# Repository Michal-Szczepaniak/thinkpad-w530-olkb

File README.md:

# Thinkpad OLKB Preonic keybaord pcb

Get it printed and enjoy.

USB can be connected in multiple ways:

- Directly into the MCU thanks to open space near it
- After soldering the bottom pads, via available pins next to the usb port
- After soldering the bottom pads and FPC connector, via FPC connector

USB can be fetched from multiple places, the lower end the laptop (x series) the less options so I'll list all the w530 options:

- Bluetooth connector, if you swapped wifi card for wifi+bt you aren't using the standalone bt so you can get usb from there
- msata, its next to the open hole for the usb, with msata to usb converter you can either just plug in short cable from msata directly to mcu (easiest possible connection) or you can cut the microusb end and solder it to pins or desolder the usb and route it with wires
- Smartcard fpc connector, it's located at the bottom middle of the motheboard next to the bios chips underneath the touchpad. Thats what the FPC connector on keyboard is for, you can buy 6 pin 0.5mm pitch FPC cable and connect it. Watch out though because it has 5V 15A unfused and if you short it you will instantly kill the laptop, but the keyboard has fuse which protects it, but only if something happens AFTER the fuse so isolate the fpc connector pins.
- Fingerprint/color sensor usb FPC, they're both just usb's on FPC tape, so you can use that, although they might not be directly pluggable into keyboard's FPC connector, I don't know their pinout as I was targetting the Smartcard FPC connector.

Power button is connected via mounting OG keyboard's FPC tape or soldering it, you can pick either option by soldering the pads next to the FPC pins. Make sure you pick correct option otherwise you can short something. Power button is also routed to the mcu pin in case you want that, although when laptop is off, they keyboard is off unless you route always-on 5V to it.

There are pins for connecting Framework touchpad, if you go this route, just wire them to the test pads on the Framework's touchpad and that's it. If you want to use Framework's touchpad and mount it by demeling the case then you need to break out the touchpad pcb extension.

There's hole for a keyboard mounting screw, M2x20 and use a nut to hold it down but don't overtighten it!

Oh also cake the bottom in electrical tape and make sure there are no pointy solder points, otherwise it will short out on the aluminum case which is less than ideal.

As of now the space above keyboard is not covered by anything which is KIIIIIIINDA sketchy but can be covered with electrical tape or simple 3D print. If you don't use the hole for usb cable that one can also be covered via electrical tape.

# 3D Printable blanks

Because the keyboard has gaping hole in the middle for the usb cable and also gaping hole above it, there are 3D printable blanks that can be put in place to protect anything below. Also if you decide to mod the touchpad I've included the touchpad buttons blank. [Blanks directory](https://github.com/Michal-Szczepaniak/thinkpad-w530-olkb)

# BOM 

- FPC 6PIN 0.5mm pitch, opposite side. Also please be careful because if you wire it incorrectly you'll instantly fry the motherboard.
- 6 pin FPC connector - DS1020-11-6VBT1-R
- Raspberry pi pico
- PG1425 switches
- Either THT or SMD diodes - THT you can handle, SMD 1N4148WS-DIO (SOD323F)
- Patience

# Palm rejection not working 

By default both framework touchpad and this keyboard are treated as external devices so we have to tell libinput that they're in fact not.

Create file `/etc/libinput/local-overrides.quirks` with content:
```
[Keyboards]
MatchUdevType=keyboard
MatchName=QMK Macroboard
AttrKeyboardIntegration=internal

[Touchpad]
MatchUdevType=touchpad
MatchName=QMK Macroboard Touchpad
AttrKeyboardIntegration=internal
```

And enable palm rejection. Voila!

# Gallery

## Schematic

## Board

## 3D View

## Real photo

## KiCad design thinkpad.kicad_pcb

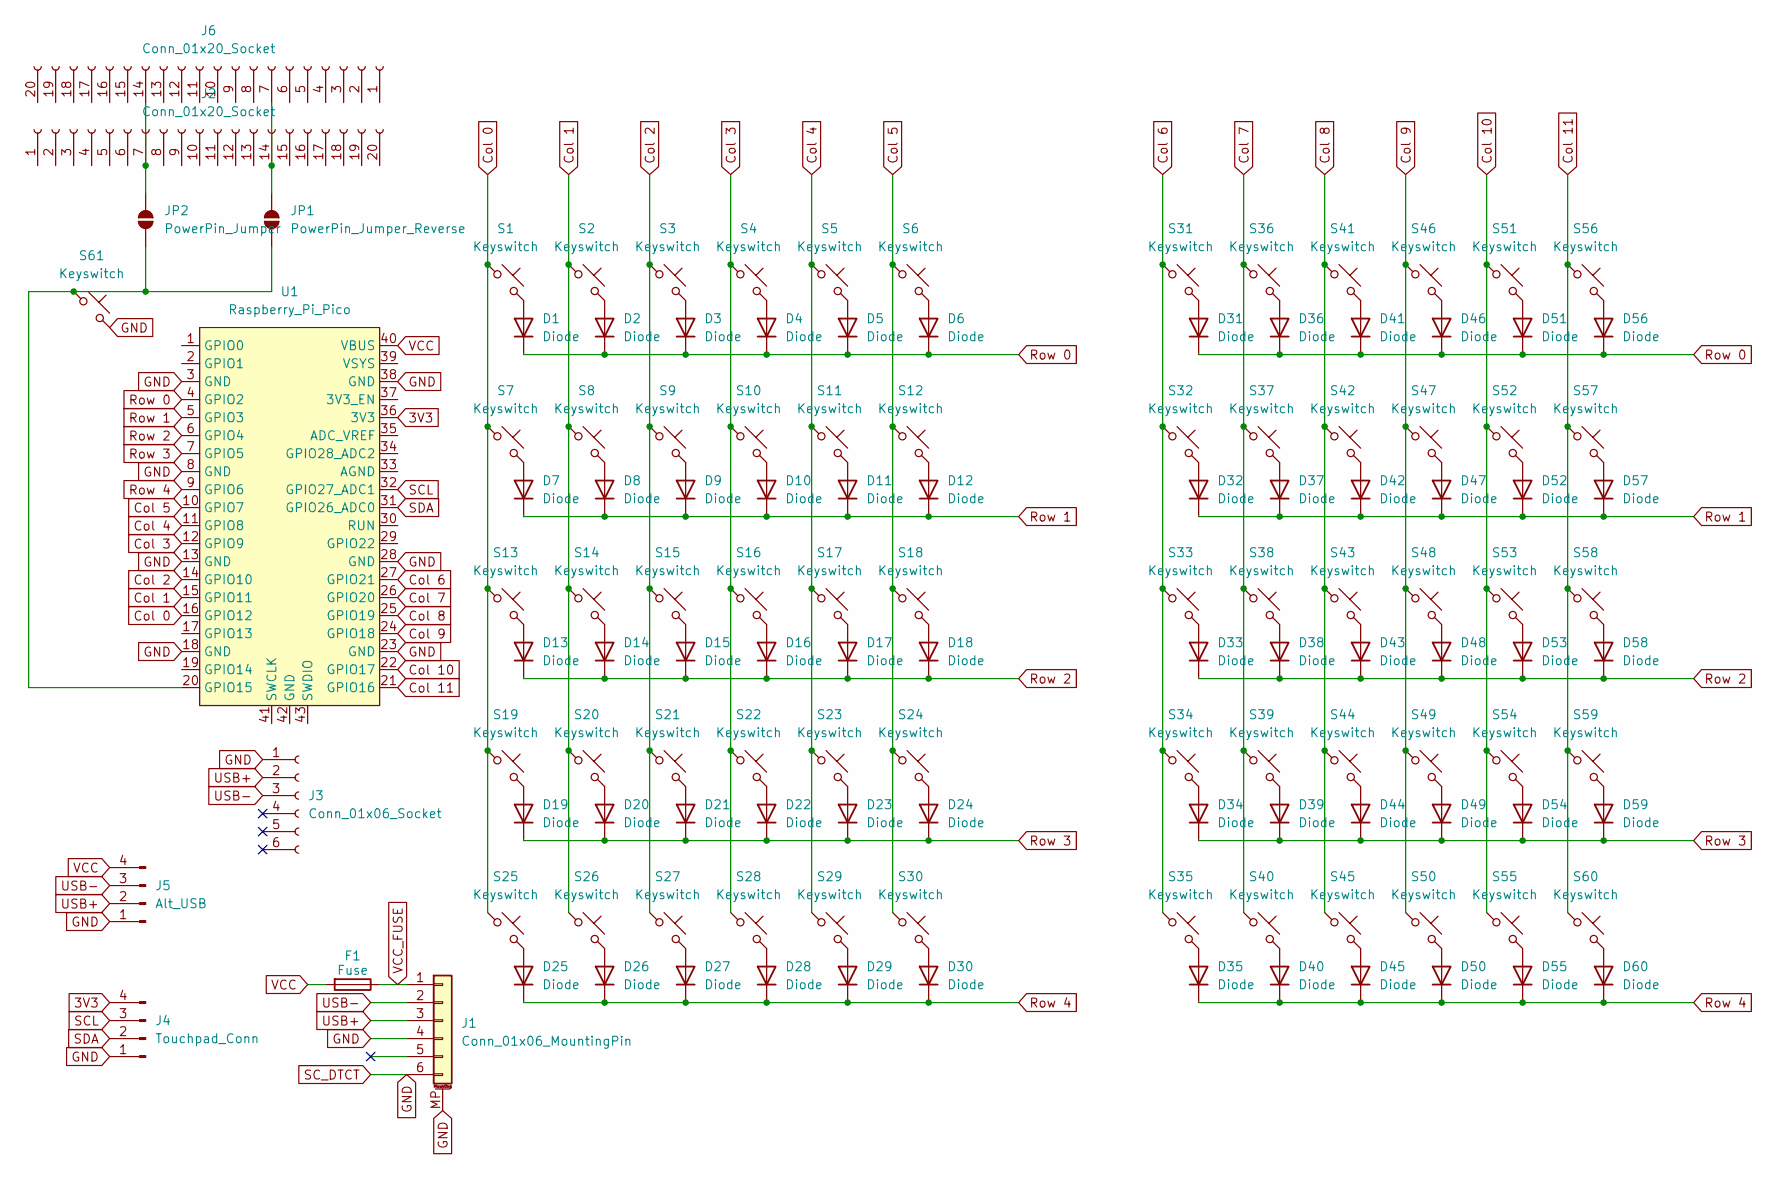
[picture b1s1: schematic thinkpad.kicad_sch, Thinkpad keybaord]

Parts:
D1, D2, D3, D4, D5, D6, D7, D8, D9, D10, D11, D12, D13, D14, D15, D16, D17, D18, D19, D20, D21, D22, D23, D24, D25, D26, D27, D28, D29, D30, D31, D32, D33, D34, D35, D36, D37, D38, D39, D40, D41, D42, D43, D44, D45, D46, D47, D48, D49, D50, D51, D52, D53, D54, D55, D56, D57, D58, D59, D60: Diode; Diode_SMD_THT2
F1: Fuse; Fuse_0805_2012Metric
J1: Conn_01x06_MountingPin; FPC_6
J2, J6: Conn_01x20_Socket; Thinkpad-keyboard-fpc
J3: Conn_01x06_Socket; pi pico usb
J4: Touchpad_Conn; PinHeader_1x04_P2.54mm_Vertical
J5: Alt_USB; PinHeader_1x04_P2.54mm_Vertical
JP1: PowerPin_Jumper_Reverse; SolderJumper-2_P1.3mm_Open_Pad1.0x1.5mm
JP2: PowerPin_Jumper; SolderJumper-2_P1.3mm_Open_Pad1.0x1.5mm
S1, S2, S3, S4, S5, S6, S7, S8, S9, S10, S11, S12, S13, S14, S15, S16, S17, S18, S19, S20, S21, S22, S23, S24, S25, S26, S27, S28, S29, S30, S31, S32, S33, S34, S35, S36, S37, S38, S39, S40, S41, S42, S43, S44, S45, S46, S47, S48, S49, S50, S51, S52, S53, S54, S55, S56, S57, S58, S59, S60, S61: Keyswitch; Kailh-PG1425-X-Switch
U1: Raspberry_Pi_Pico

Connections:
3V3: J4.4, U1.36 (3V3)
Col 0: S1.1, S7.1, S13.1, S19.1, S25.1, U1.16 (GPIO12)
Col 1: S2.1, S8.1, S14.1, S20.1, S26.1, U1.15 (GPIO11)
Col 2: S3.1, S9.1, S15.1, S21.1, S27.1, U1.14 (GPIO10)
Col 3: S4.1, S10.1, S16.1, S22.1, S28.1, U1.12 (GPIO9)
Col 4: S5.1, S11.1, S17.1, S23.1, S29.1, U1.11 (GPIO8)
Col 5: S6.1, S12.1, S18.1, S24.1, S30.1, U1.10 (GPIO7)
Col 6: S31.1, S32.1, S33.1, S34.1, S35.1, U1.27 (GPIO21)
Col 7: S36.1, S37.1, S38.1, S39.1, S40.1, U1.26 (GPIO20)
Col 8: S41.1, S42.1, S43.1, S44.1, S45.1, U1.25 (GPIO19)
Col 9: S46.1, S47.1, S48.1, S49.1, S50.1, U1.24 (GPIO18)
Col 10: S51.1, S52.1, S53.1, S54.1, S55.1, U1.22 (GPIO17)
Col 11: S56.1, S57.1, S58.1, S59.1, S60.1, U1.21 (GPIO16)
GND: J1.4, J1.6, J1.MP (MountPin), J3.1, J4.1, J5.1, S61.2, U1.3 (GND), U1.8 (GND), U1.13 (GND), U1.18 (GND), U1.23 (GND), U1.28 (GND), U1.38 (GND)
unnamed: D1.2 (A), S1.2
unnamed: D2.2 (A), S2.2
unnamed: D3.2 (A), S3.2
unnamed: D4.2 (A), S4.2
unnamed: D5.2 (A), S5.2
unnamed: D6.2 (A), S6.2
unnamed: D7.2 (A), S7.2
unnamed: D8.2 (A), S8.2
unnamed: D9.2 (A), S9.2
unnamed: D10.2 (A), S10.2
unnamed: D11.2 (A), S11.2
unnamed: D12.2 (A), S12.2
unnamed: D13.2 (A), S13.2
unnamed: D14.2 (A), S14.2
unnamed: D15.2 (A), S15.2
unnamed: D16.2 (A), S16.2
unnamed: D17.2 (A), S17.2
unnamed: D18.2 (A), S18.2
unnamed: D19.2 (A), S19.2
unnamed: D20.2 (A), S20.2
unnamed: D21.2 (A), S21.2
unnamed: D22.2 (A), S22.2
unnamed: D23.2 (A), S23.2
unnamed: D24.2 (A), S24.2
unnamed: D25.2 (A), S25.2
unnamed: D26.2 (A), S26.2
unnamed: D27.2 (A), S27.2
unnamed: D28.2 (A), S28.2
unnamed: D29.2 (A), S29.2
unnamed: D30.2 (A), S30.2
unnamed: D31.2 (A), S31.2
unnamed: D32.2 (A), S32.2
unnamed: D33.2 (A), S33.2
unnamed: D34.2 (A), S34.2
unnamed: D35.2 (A), S35.2
unnamed: D36.2 (A), S36.2
unnamed: D37.2 (A), S37.2
unnamed: D38.2 (A), S38.2
unnamed: D39.2 (A), S39.2
unnamed: D40.2 (A), S40.2
unnamed: D41.2 (A), S41.2
unnamed: D42.2 (A), S42.2
unnamed: D43.2 (A), S43.2
unnamed: D44.2 (A), S44.2
unnamed: D45.2 (A), S45.2
unnamed: D46.2 (A), S46.2
unnamed: D47.2 (A), S47.2
unnamed: D48.2 (A), S48.2
unnamed: D49.2 (A), S49.2
unnamed: D50.2 (A), S50.2
unnamed: D51.2 (A), S51.2
unnamed: D52.2 (A), S52.2
unnamed: D53.2 (A), S53.2
unnamed: D54.2 (A), S54.2
unnamed: D55.2 (A), S55.2
unnamed: D56.2 (A), S56.2
unnamed: D57.2 (A), S57.2
unnamed: D58.2 (A), S58.2
unnamed: D59.2 (A), S59.2
unnamed: D60.2 (A), S60.2
unnamed: J2.7, J6.14, JP2.2 (B)
unnamed: J2.14, J6.7, JP1.2 (B)
unnamed: JP1.1 (A), JP2.1 (A), S61.1, U1.20 (GPIO15)
Row 0: D1.1 (K), D2.1 (K), D3.1 (K), D4.1 (K), D5.1 (K), D6.1 (K), D31.1 (K), D36.1 (K), D41.1 (K), D46.1 (K), D51.1 (K), D56.1 (K), U1.4 (GPIO2)
Row 1: D7.1 (K), D8.1 (K), D9.1 (K), D10.1 (K), D11.1 (K), D12.1 (K), D32.1 (K), D37.1 (K), D42.1 (K), D47.1 (K), D52.1 (K), D57.1 (K), U1.5 (GPIO3)
Row 2: D13.1 (K), D14.1 (K), D15.1 (K), D16.1 (K), D17.1 (K), D18.1 (K), D33.1 (K), D38.1 (K), D43.1 (K), D48.1 (K), D53.1 (K), D58.1 (K), U1.6 (GPIO4)
Row 3: D19.1 (K), D20.1 (K), D21.1 (K), D22.1 (K), D23.1 (K), D24.1 (K), D34.1 (K), D39.1 (K), D44.1 (K), D49.1 (K), D54.1 (K), D59.1 (K), U1.7 (GPIO5)
Row 4: D25.1 (K), D26.1 (K), D27.1 (K), D28.1 (K), D29.1 (K), D30.1 (K), D35.1 (K), D40.1 (K), D45.1 (K), D50.1 (K), D55.1 (K), D60.1 (K), U1.9 (GPIO6)
SCL: J4.3, U1.32 (GPIO27_ADC1)
SDA: J4.2, U1.31 (GPIO26_ADC0)
USB+: J1.3, J3.2, J5.2
USB-: J1.2, J3.3, J5.3
VCC: F1.2, J5.4, U1.40 (VBUS)
VCC_FUSE: F1.1, J1.1

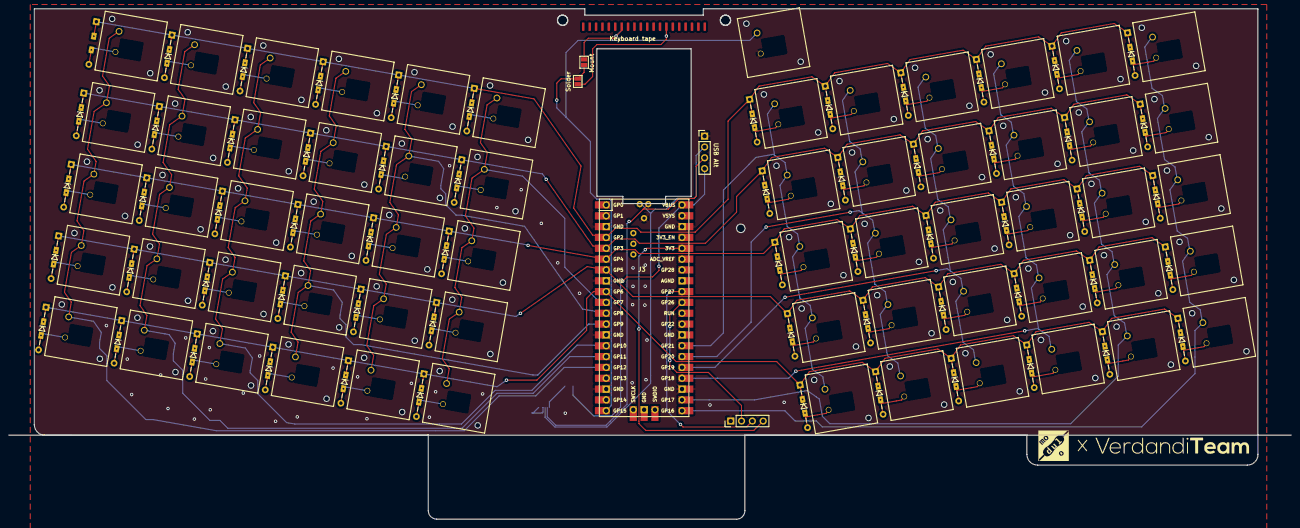
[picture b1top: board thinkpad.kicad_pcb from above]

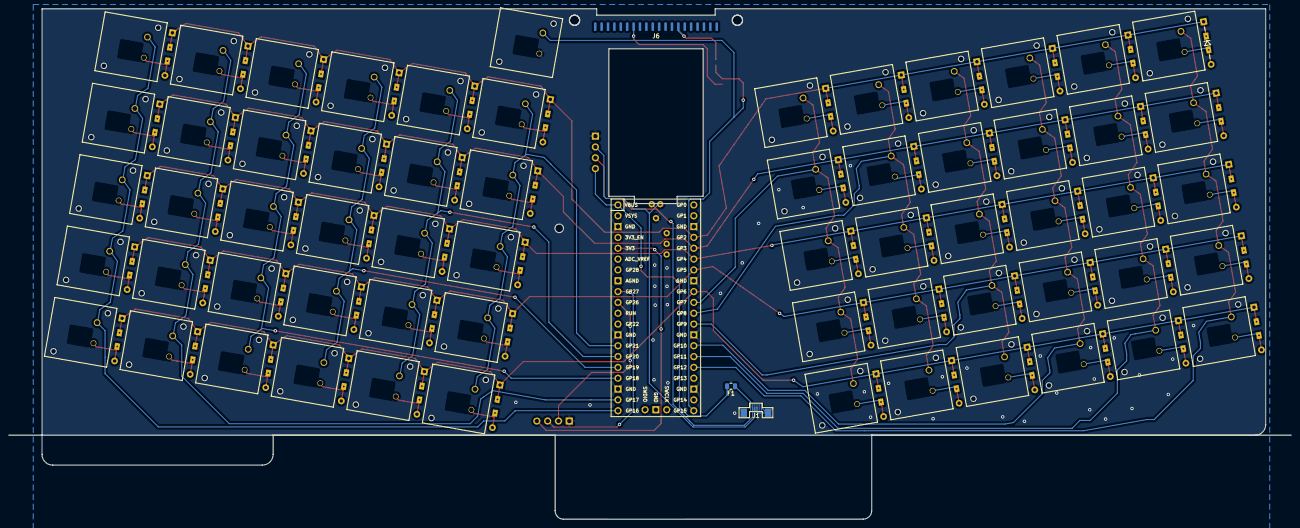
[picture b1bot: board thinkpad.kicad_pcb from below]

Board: 2 copper layers, 300.8 x 119.7 mm, 131 parts (4 on the bottom side), 88 nets.

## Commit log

2023-11-22 Add README.md
2023-11-22 Fix gnd
2023-11-22 Improvements
2023-11-29 Made space for touchpad, fixed connection of cols, added pads for touchpad i2c
2023-11-29 Give 3V3 to touchpad
2024-04-22 Fix issue with usb and aligning the tape
2024-12-21 Change switches
2025-02-25 Fix issues and add breakable touchpad
2025-02-25 Update pictures
2025-02-25 Fix picture
2025-02-25 Add real photo
2025-02-25 Fix real photo
2025-02-26 filled zones set to no-island, vias added to make ground fills appear in more places (mostly aesthetic), keeb connector duuplicated, drc clean, unconnected 0, life is good
2025-04-02 Update BOM
2025-04-09 Update FPC info
2025-04-10 Update real photo
2025-04-22 Add blanks
2025-04-25 Add palm rejection instructions
